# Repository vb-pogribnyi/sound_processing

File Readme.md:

## Sound Processing
This repository contains imlementation of sound localization methods. It contains parts such as:
- data generation ```Generation``` directory
- processing of open MMAUD dataset in ```Training/Processing/MMAUD```
- processing of the generated dataset(s) in  ```Training/Processing/KWave```
- implementations of top-performing models at the moment in ```Training/NN``` directory
- two most popular types of signal feature extractors: mel-spectrogram and SRP, with root file in ```Training/Data/loader.py```
- unified training pipeline in ```Training/train.py```

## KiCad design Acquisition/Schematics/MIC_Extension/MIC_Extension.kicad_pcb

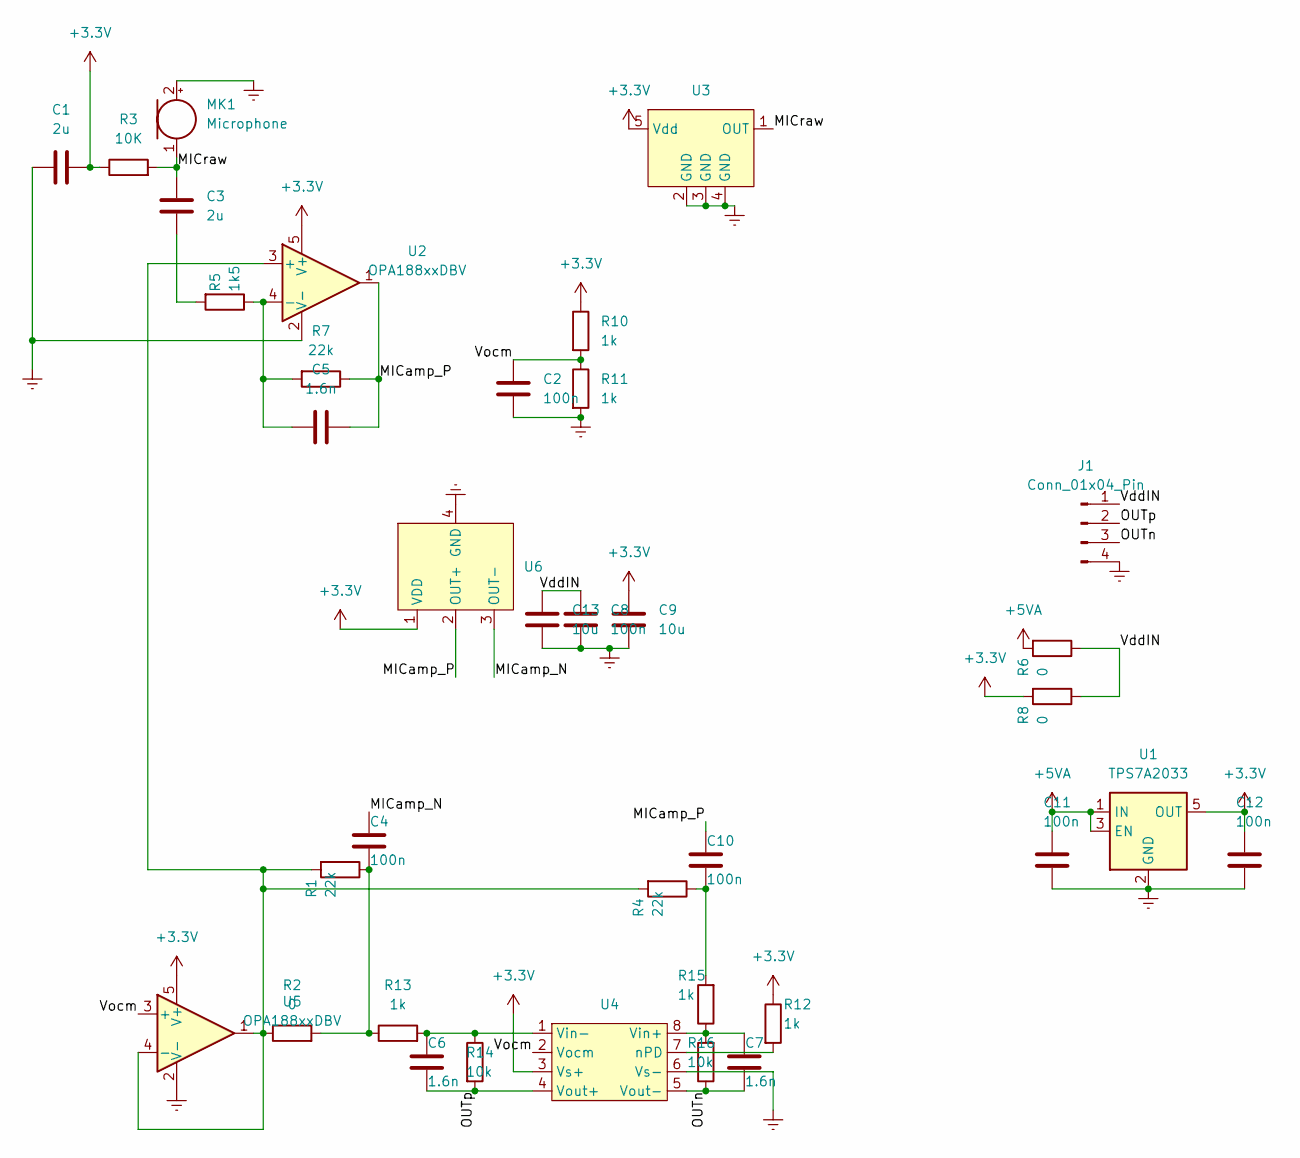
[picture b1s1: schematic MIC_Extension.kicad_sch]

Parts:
C1, C3: 2u; C_0603_1608Metric
C2, C4, C8, C10, C11, C12: 100n; C_0603_1608Metric
C5, C6, C7: 1.6n; C_0603_1608Metric
C9, C13: 10u; C_0603_1608Metric
J1: Conn_01x04_Pin; PinHeader_1x04_P2.54mm_Vertical
MK1: Microphone; PinHeader_1x02_P2.54mm_Vertical
R1, R4, R7: 22k; C_0603_1608Metric
R2, R6, R8: 0; C_0603_1608Metric
R3: 10K; C_0603_1608Metric
R5: 1k5; C_0603_1608Metric
R10, R11, R12, R13, R15: 1k; C_0603_1608Metric
R14, R16: 10k; C_0603_1608Metric
U1: TPS7A2033; SOT-23-5
U2, U5: OPA188xxDBV; TSOT-23-5
U3: AMP23
U4: VSSOP-8_3.0x3.0mm_P0.65mm
U6: ICS-40730

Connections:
+3.3V: C1.2, C9.1, C12.1, R3.1, R8.2, R10.1, R12.1, U1.5 (OUT), U2.5 (V+), U3.5 (Vdd), U4.3 (Vs+), U5.5 (V+), U6.1 (VDD)
+5VA: C11.1, R6.2, U1.1 (IN), U1.3 (EN)
/MICamp_N: C4.2, U6.3 (OUT-)
/MICamp_P: C5.2, C10.2, R7.1, U2.1, U6.2 (OUT+)
/MICraw: C3.1, MK1.1 (-), R3.2, U3.1 (OUT)
/OUTn: C7.1, J1.3, R16.1, U4.5 (Vout-)
/OUTp: C6.1, J1.2, R14.2, U4.4 (Vout+)
/VddIN: C8.1, C13.1, J1.1, R6.1, R8.1
/Vocm: C2.1, R10.2, R11.1, U4.2 (Vocm), U5.3 (+)
Earth: C1.1, C2.2, C8.2, C9.2, C11.2, C12.2, C13.2, J1.4, MK1.2 (+), R11.2, U1.2 (GND), U2.2 (V-), U3.2 (GND), U3.3 (GND), U3.4 (GND), U4.6 (Vs-), U5.2 (V-), U6.4 (GND)
unnamed: C3.2, R5.2
unnamed: C4.1, R1.1, R2.2, R13.1
unnamed: C10.1, R4.1, R15.2
unnamed: R1.2, R2.1, R4.2, U2.3 (+), U5.1, U5.4 (-)
unnamed: C5.1, R5.1, R7.2, U2.4 (-)
unnamed: C7.2, R15.1, R16.2, U4.8 (Vin+)
unnamed: C6.2, R13.2, R14.1, U4.1 (Vin-)
unnamed: R12.2, U4.7 (nPD)

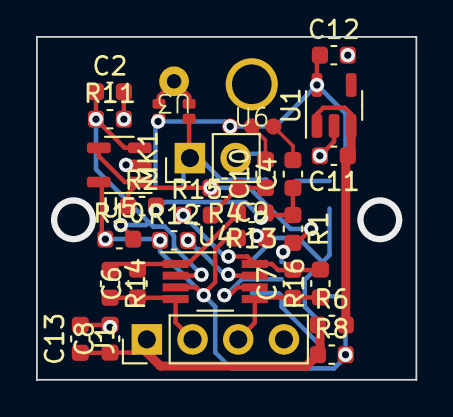
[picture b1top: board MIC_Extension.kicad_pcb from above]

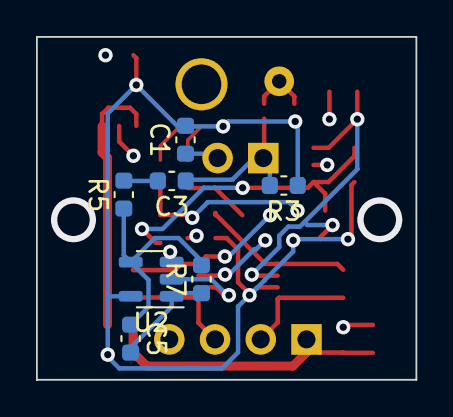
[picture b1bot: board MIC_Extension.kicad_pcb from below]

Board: 4 copper layers, 21.1 x 19.1 mm, 36 parts (7 on the bottom side), 18 nets.

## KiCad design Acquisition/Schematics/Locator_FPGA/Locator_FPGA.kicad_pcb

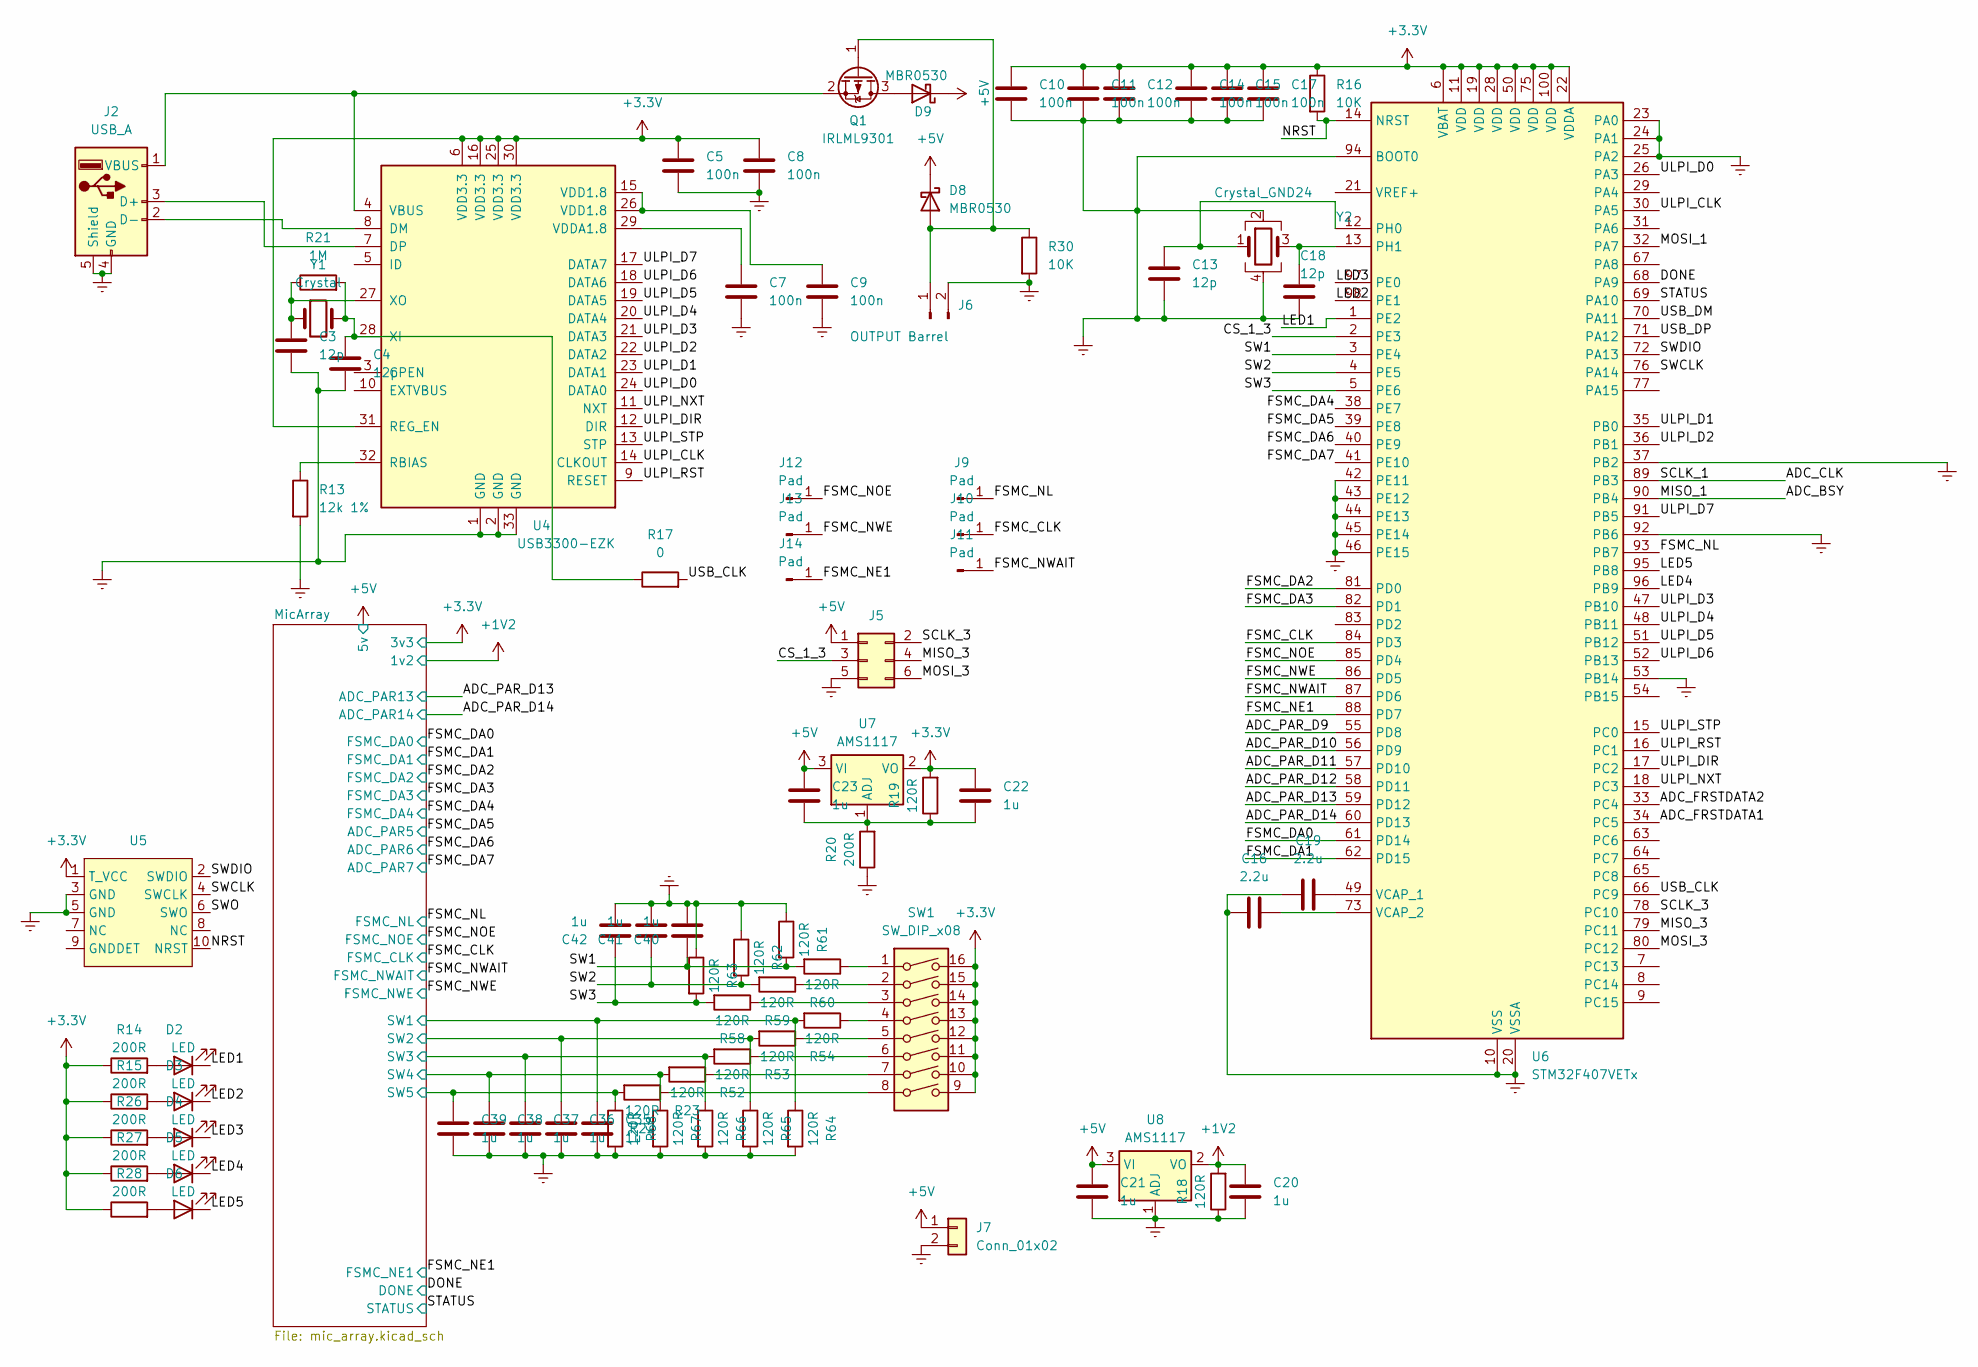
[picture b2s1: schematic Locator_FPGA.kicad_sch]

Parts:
C3, C4, C13, C18: 12p; C_0603_1608Metric
C5, C7, C8, C9: 100n; C_0603_1608Metric
C10, C11, C12, C14, C15, C17: 100n; C_0402_1005Metric
C16, C19: 2.2u; C_0603_1608Metric
C20, C21, C22, C23, C35, C36, C37, C38, C39, C40, C41, C42: 1u; C_0603_1608Metric
D2, D3, D4, D5, D6: LED; LED_0805_2012Metric
D8, D9: MBR0530; D_SOD-123
J2: USB_A; USB_A_CONNFLY_DS1095-WNR0
J5: Conn_02x03_Odd_Even; PinSocket_2x03_P2.00mm_Vertical
J6: OUTPUT Barrel; PinHeader_1x02_P2.54mm_Vertical
J7: Conn_01x02; PinHeader_1x02_P2.54mm_Vertical
J9, J10, J11, J12, J13, J14: Pad
Q1: IRLML9301; SOT-23
R13: 12k 1%; C_0603_1608Metric
R14, R15, R20, R26, R27, R28: 200R; R_0603_1608Metric
R16, R30: 10K; C_0603_1608Metric
R17: 0; C_0603_1608Metric
R18, R19, R22, R23, R52, R53, R54, R58, R59, R60, R61, R62, R63, R64, R65, R66, R67, R68: 120R; R_0603_1608Metric
R21: 1M; C_0603_1608Metric
SW1: SW_DIP_x08; DIP-16_W7.62mm
U4: USB3300-EZK; QFN-32-1EP_5x5mm_P0.5mm_EP3.45x3.45mm
U5: PinHeader_2x05_P1.27mm_Vertical_SMD
U6: STM32F407VETx; LQFP-100_14x14mm_P0.5mm
U7, U8: AMS1117; SOT-223-3_TabPin2
Y1: Crystal; Crystal_SMD_MicroCrystal_CC7V-T1A-2Pin_3.2x1.5mm
Y2: Crystal_GND24; Crystal_SMD_Abracon_ABM3C-4Pin_5.0x3.2mm

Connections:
+1V2: C20.1, R18.2, U8.2 (VO); also elsewhere on the board
+3.3V: C5.1, C8.1, C10.1, C11.1, C12.1, C14.1, C15.1, C17.1, C22.1, R14.1, R15.1, R16.1, R19.2, R26.1, R27.1, R28.1, SW1.9, SW1.10, SW1.11, SW1.12, SW1.13, SW1.14, SW1.15, SW1.16, U4.6 (VDD3.3), U4.16 (VDD3.3), U4.25 (VDD3.3), U4.30 (VDD3.3), U4.31 (REG_EN), U5.1 (T_VCC), U6.6 (VBAT), U6.11 (VDD), U6.19 (VDD), U6.22 (VDDA), U6.28 (VDD), U6.50 (VDD), U6.75 (VDD), U6.100 (VDD), U7.2 (VO); also elsewhere on the board
+5V: C21.1, C23.1, D8.1 (K), D9.1 (K), J5.1, J7.1, U7.3 (VI), U8.3 (VI); also elsewhere on the board
/ADC_BSY: U6.90 (PB4)
/ADC_CLK: U6.89 (PB3)
/ADC_FRSTDATA1: U6.34 (PC5)
/ADC_FRSTDATA2: U6.33 (PC4)
/ADC_PAR_D9: U6.55 (PD8)
/ADC_PAR_D10: U6.56 (PD9)
/ADC_PAR_D11: U6.57 (PD10)
/ADC_PAR_D12: U6.58 (PD11)
/ADC_PAR_D13: U6.59 (PD12)
/ADC_PAR_D14: U6.60 (PD13)
/CS_1_3: J5.3, U6.2 (PE3)
/DONE: U6.68 (PA9); also elsewhere on the board
/FSMC_CLK: J10.1, U6.84 (PD3); also elsewhere on the board
/FSMC_DA0: U6.61 (PD14); also elsewhere on the board
/FSMC_DA1: U6.62 (PD15); also elsewhere on the board
/FSMC_DA2: U6.81 (PD0); also elsewhere on the board
/FSMC_DA3: U6.82 (PD1); also elsewhere on the board
/FSMC_DA4: U6.38 (PE7); also elsewhere on the board
/FSMC_DA5: U6.39 (PE8); also elsewhere on the board
/FSMC_DA6: U6.40 (PE9); also elsewhere on the board
/FSMC_DA7: U6.41 (PE10); also elsewhere on the board
/FSMC_NE1: J14.1, U6.88 (PD7); also elsewhere on the board
/FSMC_NL: J9.1, U6.93 (PB7); also elsewhere on the board
/FSMC_NOE: J12.1, U6.85 (PD4); also elsewhere on the board
/FSMC_NWAIT: J11.1, U6.87 (PD6); also elsewhere on the board
/FSMC_NWE: J13.1, U6.86 (PD5); also elsewhere on the board
/LED1: D2.1 (K), U6.1 (PE2)
/LED2: D3.1 (K), U6.98 (PE1)
/LED3: D4.1 (K), U6.97 (PE0)
/LED4: D5.1 (K), U6.96 (PB9)
/LED5: D6.1 (K), U6.95 (PB8)
/MISO_3: J5.4, U6.79 (PC11)
/MOSI_1: U6.32 (PA7)
/MOSI_3: J5.6, U6.80 (PC12)
/MicArray/SW1: C35.1, R54.2, R64.1; also elsewhere on the board
/MicArray/SW2: C36.1, R53.2, R65.1; also elsewhere on the board
/MicArray/SW3: C37.1, R52.2, R66.1; also elsewhere on the board
/MicArray/SW4: C38.1, R23.2, R67.1; also elsewhere on the board
/MicArray/SW5: C39.1, R22.2, R68.1; also elsewhere on the board
/NRST: R16.2, U5.10 (NRST), U6.14 (NRST)
/SCLK_3: J5.2, U6.78 (PC10)
/STATUS: U6.69 (PA10); also elsewhere on the board
/SW1: C40.1, R60.2, R61.2, U6.3 (PE4)
/SW2: C41.1, R59.2, R62.2, U6.4 (PE5)
/SW3: C42.1, R58.2, R63.2, U6.5 (PE6)
/SWCLK: U5.4 (SWCLK), U6.76 (PA14)
/SWDIO: U5.2 (SWDIO), U6.72 (PA13)
/SWO: U5.6 (SWO)
/ULPI_CLK: U4.14 (CLKOUT), U6.30 (PA5)
/ULPI_D0: U4.24 (DATA0), U6.26 (PA3)
/ULPI_D1: U4.23 (DATA1), U6.35 (PB0)
/ULPI_D2: U4.22 (DATA2), U6.36 (PB1)
/ULPI_D3: U4.21 (DATA3), U6.47 (PB10)
/ULPI_D4: U4.20 (DATA4), U6.48 (PB11)
/ULPI_D5: U4.19 (DATA5), U6.51 (PB12)
/ULPI_D6: U4.18 (DATA6), U6.52 (PB13)
/ULPI_D7: U4.17 (DATA7), U6.91 (PB5)
/ULPI_DIR: U4.12 (DIR), U6.17 (PC2)
/ULPI_NXT: U4.11 (NXT), U6.18 (PC3)
/ULPI_RST: U4.9 (RESET), U6.16 (PC1)
/ULPI_STP: U4.13 (STP), U6.15 (PC0)
/USB_CLK: R17.2, U6.66 (PC9)
/USB_DM: U6.70 (PA11)
/USB_DP: U6.71 (PA12)
Earth: C3.2, C4.2, C5.2, C7.2, C8.2, C9.2, C10.2, C11.2, C12.2, C13.2, C14.2, C15.2, C16.1, C17.2, C18.2, C19.1, C20.2, C21.2, C35.2, C36.2, C37.2, C38.2, C39.2, C40.2, C41.2, C42.2, J2.4 (GND), J2.5 (Shield), J5.5, J6.2, J7.2, R13.2, R18.1, R20.1, R30.2, R61.1, R62.1, R63.1, R64.2, R65.2, R66.2, R67.2, R68.2, U4.1 (GND), U4.2 (GND), U4.33 (GND), U5.3 (GND), U5.5 (GND), U6.10 (VSS), U6.20 (VSSA), U6.23 (PA0), U6.24 (PA1), U6.25 (PA2), U6.27 (VSS), U6.37 (PB2), U6.42 (PE11), U6.43 (PE12), U6.44 (PE13), U6.45 (PE14), U6.46 (PE15), U6.53 (PB14), U6.74 (VSS), U6.92 (PB6), U6.94 (BOOT0), U6.99 (VSS), U8.1 (ADJ), Y2.2, Y2.4; also elsewhere on the board
unnamed: C9.1, U4.15 (VDD1.8), U4.26 (VDD1.8)
unnamed: D2.2 (A), R14.2
unnamed: D3.2 (A), R15.2
unnamed: D4.2 (A), R26.2
unnamed: D5.2 (A), R27.2
unnamed: D6.2 (A), R28.2
unnamed: D8.2 (A), J6.1, Q1.1 (G), R30.1
unnamed: D9.2 (A), Q1.3 (D)
unnamed: J2.3 (D+), U4.7 (DP)
unnamed: J2.2 (D-), U4.8 (DM)
unnamed: J2.1 (VBUS), Q1.2 (S), U4.4 (VBUS)
unnamed: R22.1, SW1.8
unnamed: R23.1, SW1.7
unnamed: R52.1, SW1.6
unnamed: R53.1, SW1.5
unnamed: R54.1, SW1.4
unnamed: R58.1, SW1.3
unnamed: R59.1, SW1.2
unnamed: R60.1, SW1.1
unnamed: R13.1, U4.32 (RBIAS)
unnamed: C7.1, U4.29 (VDDA1.8)
unnamed: C4.1, R17.1, R21.2, U4.28 (XI), Y1.2
unnamed: C3.1, R21.1, U4.27 (XO), Y1.1
unnamed: C13.1, U6.12 (PH0), Y2.1
unnamed: C18.1, U6.13 (PH1), Y2.3
unnamed: C19.2, U6.49 (VCAP_1)
unnamed: C16.2, U6.73 (VCAP_2)
unnamed: C22.2, C23.2, R19.1, R20.2, U7.1 (ADJ)

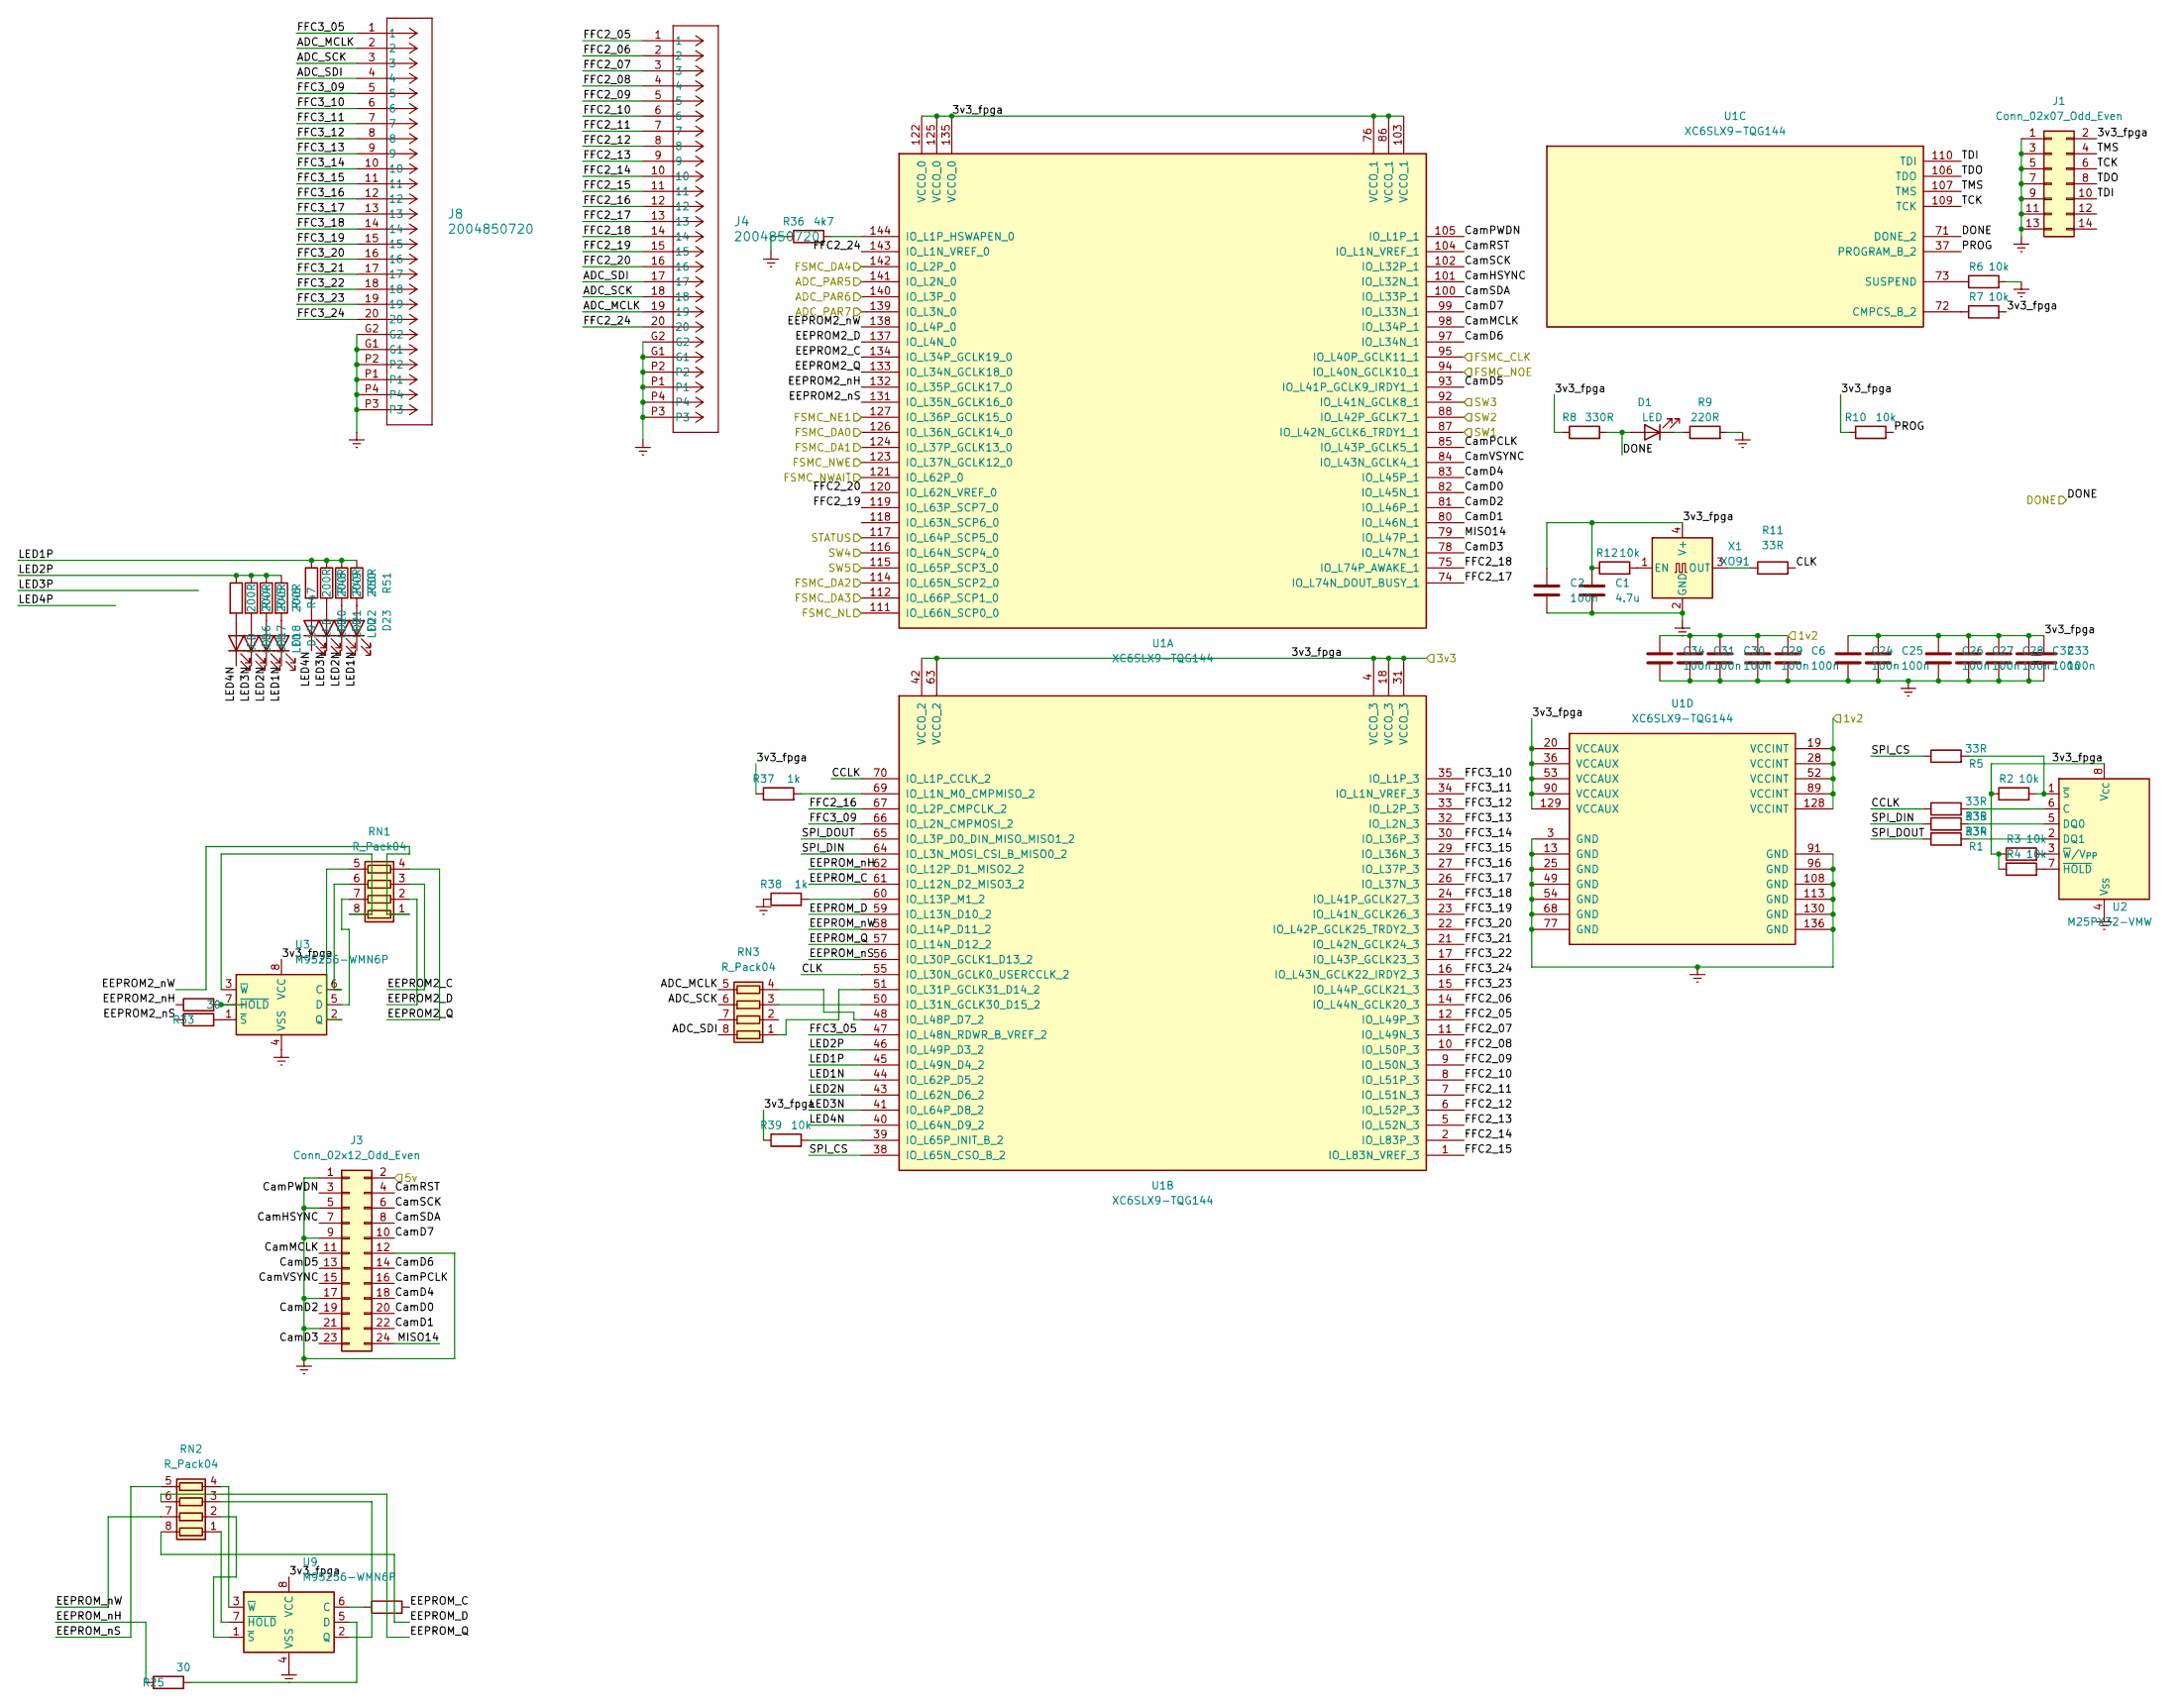
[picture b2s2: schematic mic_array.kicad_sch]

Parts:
C1: 4.7u; R_0603_1608Metric
C2: 100n; R_0603_1608Metric
C6, C24, C25, C26, C27, C28, C29, C30, C31, C32, C33, C34: 100n; C_0402_1005Metric
D1, D16, D17, D18, D19, D20, D21, D22, D23: LED; LED_0805_2012Metric
J1: Conn_02x07_Odd_Even; PinHeader_2x07_P2.00mm_Vertical
J3: Conn_02x12_Odd_Even; PinHeader_2x12_P2.54mm_Vertical
J4, J8: 2004850720; Molex FFC 20pin sideways
R1, R5, R11, R34, R35: 33R; R_0603_1608Metric
R2, R3, R4, R6, R7, R10, R12, R39: 10k; R_0603_1608Metric
R8: 330R; R_0603_1608Metric
R9: 220R; R_0603_1608Metric
R24, R25, R29, R33: 30; R_0603_1608Metric
R36: 4k7; R_0603_1608Metric
R37, R38: 1k; R_0603_1608Metric
R44, R45, R46, R47, R48, R49, R50, R51: 200R; R_0603_1608Metric
RN1, RN2, RN3: R_Pack04; R_Array_Concave_4x0402
U1: XC6SLX9-TQG144; TQFP-144_20x20mm_P0.5mm
U2: M25PX32-VMW; SOIC-8W_5.3x5.3mm_P1.27mm
U3, U9: M95256-WMN6P; SOIC-8_3.9x4.9mm_P1.27mm
X1: XO91; Oscillator_SMD_EuroQuartz_XO91-4Pin_7.0x5.0mm

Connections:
+1V2: C6.1, C29.1, C30.1, C31.1, C34.1, U1.19 (VCCINT), U1.28 (VCCINT), U1.52 (VCCINT), U1.89 (VCCINT), U1.128 (VCCINT); also elsewhere on the board
+3.3V: C1.1, C2.1, C24.1, C25.1, C26.1, C27.1, C28.1, C32.1, C33.1, J1.2, R2.1, R3.1, R4.1, R7.2, R8.1, R10.1, R12.1, R37.1, R39.1, U1.4 (VCCO_3), U1.18 (VCCO_3), U1.20 (VCCAUX), U1.31 (VCCO_3), U1.36 (VCCAUX), U1.42 (VCCO_2), U1.53 (VCCAUX), U1.63 (VCCO_2), U1.76 (VCCO_1), U1.86 (VCCO_1), U1.90 (VCCAUX), U1.103 (VCCO_1), U1.122 (VCCO_0), U1.125 (VCCO_0), U1.129 (VCCAUX), U1.135 (VCCO_0), U2.8 (V_{CC}), U3.8 (VCC), U9.8 (VCC), X1.4 (V+); also elsewhere on the board
+5V: J3.2; also elsewhere on the board
/DONE: D1.2 (A), R8.2, U1.71 (DONE_2); also elsewhere on the board
/FSMC_CLK: U1.95 (IO_L40P_GCLK11_1); also elsewhere on the board
/FSMC_DA0: U1.126 (IO_L36N_GCLK14_0); also elsewhere on the board
/FSMC_DA1: U1.124 (IO_L37P_GCLK13_0); also elsewhere on the board
/FSMC_DA2: U1.114 (IO_L65N_SCP2_0); also elsewhere on the board
/FSMC_DA3: U1.112 (IO_L66P_SCP1_0); also elsewhere on the board
/FSMC_DA4: U1.142 (IO_L2P_0); also elsewhere on the board
/FSMC_DA5: U1.141 (IO_L2N_0); also elsewhere on the board
/FSMC_DA6: U1.140 (IO_L3P_0); also elsewhere on the board
/FSMC_DA7: U1.139 (IO_L3N_0); also elsewhere on the board
/FSMC_NE1: U1.127 (IO_L36P_GCLK15_0); also elsewhere on the board
/FSMC_NL: U1.111 (IO_L66N_SCP0_0); also elsewhere on the board
/FSMC_NOE: U1.94 (IO_L40N_GCLK10_1); also elsewhere on the board
/FSMC_NWAIT: U1.121 (IO_L62P_0); also elsewhere on the board
/FSMC_NWE: U1.123 (IO_L37N_GCLK12_0); also elsewhere on the board
/MicArray/ADC_MCLK: J4.19, J8.2, RN3.5 (R4.2)
/MicArray/ADC_SCK: J4.18, J8.3, RN3.6 (R3.2)
/MicArray/ADC_SDI: J4.17, J8.4, RN3.8 (R1.2)
/MicArray/CCLK: R35.1, U1.70 (IO_L1P_CCLK_2)
/MicArray/CLK: R11.2, U1.55 (IO_L30N_GCLK0_USERCCLK_2)
/MicArray/CamD0: J3.20, U1.82 (IO_L45N_1)
/MicArray/CamD1: J3.22, U1.80 (IO_L46N_1)
/MicArray/CamD2: J3.19, U1.81 (IO_L46P_1)
/MicArray/CamD3: J3.23, U1.78 (IO_L47N_1)
/MicArray/CamD4: J3.18, U1.83 (IO_L45P_1)
/MicArray/CamD5: J3.13, U1.93 (IO_L41P_GCLK9_IRDY1_1)
/MicArray/CamD6: J3.14, U1.97 (IO_L34N_1)
/MicArray/CamD7: J3.10, U1.99 (IO_L33N_1)
/MicArray/CamHSYNC: J3.7, U1.101 (IO_L32N_1)
/MicArray/CamMCLK: J3.11, U1.98 (IO_L34P_1)
/MicArray/CamPCLK: J3.16, U1.85 (IO_L43P_GCLK5_1)
/MicArray/CamPWDN: J3.3, U1.105 (IO_L1P_1)
/MicArray/CamRST: J3.4, U1.104 (IO_L1N_VREF_1)
/MicArray/CamSCK: J3.6, U1.102 (IO_L32P_1)
/MicArray/CamSDA: J3.8, U1.100 (IO_L33P_1)
/MicArray/CamVSYNC: J3.15, U1.84 (IO_L43N_GCLK4_1)
/MicArray/EEPROM2_C: RN1.3 (R3.1), U1.134 (IO_L34P_GCLK19_0)
/MicArray/EEPROM2_D: RN1.2 (R2.1), U1.137 (IO_L4N_0)
/MicArray/EEPROM2_Q: RN1.4 (R4.1), U1.133 (IO_L34N_GCLK18_0)
/MicArray/EEPROM2_nH: R24.1, U1.132 (IO_L35P_GCLK17_0)
/MicArray/EEPROM2_nS: R33.1, U1.131 (IO_L35N_GCLK16_0)
/MicArray/EEPROM2_nW: RN1.1 (R1.1), U1.138 (IO_L4P_0)
/MicArray/EEPROM_C: R29.2, U1.61 (IO_L12N_D2_MISO3_2)
/MicArray/EEPROM_D: RN2.8 (R1.2), U1.59 (IO_L13N_D10_2)
/MicArray/EEPROM_Q: RN2.6 (R3.2), U1.57 (IO_L14N_D12_2)
/MicArray/EEPROM_nH: R25.1, U1.62 (IO_L12P_D1_MISO2_2)
/MicArray/EEPROM_nS: RN2.5 (R4.2), U1.56 (IO_L30P_GCLK1_D13_2)
/MicArray/EEPROM_nW: RN2.7 (R2.2), U1.58 (IO_L14P_D11_2)
/MicArray/FFC2_05: J4.1, U1.12 (IO_L49P_3)
/MicArray/FFC2_06: J4.2, U1.14 (IO_L44N_GCLK20_3)
/MicArray/FFC2_07: J4.3, U1.11 (IO_L49N_3)
/MicArray/FFC2_08: J4.4, U1.10 (IO_L50P_3)
/MicArray/FFC2_09: J4.5, U1.9 (IO_L50N_3)
/MicArray/FFC2_10: J4.6, U1.8 (IO_L51P_3)
/MicArray/FFC2_11: J4.7, U1.7 (IO_L51N_3)
/MicArray/FFC2_12: J4.8, U1.6 (IO_L52P_3)
/MicArray/FFC2_13: J4.9, U1.5 (IO_L52N_3)
/MicArray/FFC2_14: J4.10, U1.2 (IO_L83P_3)
/MicArray/FFC2_15: J4.11, U1.1 (IO_L83N_VREF_3)
/MicArray/FFC2_16: J4.12, U1.67 (IO_L2P_CMPCLK_2)
/MicArray/FFC2_17: J4.13, U1.74 (IO_L74N_DOUT_BUSY_1)
/MicArray/FFC2_18: J4.14, U1.75 (IO_L74P_AWAKE_1)
/MicArray/FFC2_19: J4.15, U1.119 (IO_L63P_SCP7_0)
/MicArray/FFC2_20: J4.16, U1.120 (IO_L62N_VREF_0)
/MicArray/FFC2_24: J4.20, U1.143 (IO_L1N_VREF_0)
/MicArray/FFC3_05: J8.1, U1.47 (IO_L48N_RDWR_B_VREF_2)
/MicArray/FFC3_09: J8.5, U1.66 (IO_L2N_CMPMOSI_2)
/MicArray/FFC3_10: J8.6, U1.35 (IO_L1P_3)
/MicArray/FFC3_11: J8.7, U1.34 (IO_L1N_VREF_3)
/MicArray/FFC3_12: J8.8, U1.33 (IO_L2P_3)
/MicArray/FFC3_13: J8.9, U1.32 (IO_L2N_3)
/MicArray/FFC3_14: J8.10, U1.30 (IO_L36P_3)
/MicArray/FFC3_15: J8.11, U1.29 (IO_L36N_3)
/MicArray/FFC3_16: J8.12, U1.27 (IO_L37P_3)
/MicArray/FFC3_17: J8.13, U1.26 (IO_L37N_3)
/MicArray/FFC3_18: J8.14, U1.24 (IO_L41P_GCLK27_3)
/MicArray/FFC3_19: J8.15, U1.23 (IO_L41N_GCLK26_3)
/MicArray/FFC3_20: J8.16, U1.22 (IO_L42P_GCLK25_TRDY2_3)
/MicArray/FFC3_21: J8.17, U1.21 (IO_L42N_GCLK24_3)
/MicArray/FFC3_22: J8.18, U1.17 (IO_L43P_GCLK23_3)
/MicArray/FFC3_23: J8.19, U1.15 (IO_L44P_GCLK21_3)
/MicArray/FFC3_24: J8.20, U1.16 (IO_L43N_GCLK22_IRDY2_3)
/MicArray/LED1N: D19.1 (K), D23.1 (K), U1.44 (IO_L62P_D5_2)
/MicArray/LED1P: R48.1, R49.1, R50.1, R51.1, U1.45 (IO_L49N_D4_2)
/MicArray/LED2N: D18.1 (K), D22.1 (K), U1.43 (IO_L62N_D6_2)
/MicArray/LED2P: R44.1, R45.1, R46.1, R47.1, U1.46 (IO_L49P_D3_2)
/MicArray/LED3N: D17.1 (K), D21.1 (K), U1.41 (IO_L64P_D8_2)
/MicArray/LED4N: D16.1 (K), D20.1 (K), U1.40 (IO_L64N_D9_2)
/MicArray/MISO14: J3.24, U1.79 (IO_L47P_1)
/MicArray/PROG: R10.2, U1.37 (PROGRAM_B_2)
/MicArray/SPI_CS: R5.1, U1.38 (IO_L65N_CSO_B_2)
/MicArray/SPI_DIN: R34.1, U1.64 (IO_L3N_MOSI_CSI_B_MISO0_2)
/MicArray/SPI_DOUT: R1.1, U1.65 (IO_L3P_D0_DIN_MISO_MISO1_2)
/MicArray/SW1: U1.87 (IO_L42N_GCLK6_TRDY1_1); also elsewhere on the board
/MicArray/SW2: U1.88 (IO_L42P_GCLK7_1); also elsewhere on the board
/MicArray/SW3: U1.92 (IO_L41N_GCLK8_1); also elsewhere on the board
/MicArray/SW4: U1.116 (IO_L64N_SCP4_0); also elsewhere on the board
/MicArray/SW5: U1.115 (IO_L65P_SCP3_0); also elsewhere on the board
/MicArray/TCK: J1.6, U1.109 (TCK)
/MicArray/TDI: J1.10, U1.110 (TDI)
/MicArray/TDO: J1.8, U1.106 (TDO)
/MicArray/TMS: J1.4, U1.107 (TMS)
/STATUS: U1.117 (IO_L64P_SCP5_0); also elsewhere on the board
Earth: C1.2, C2.2, C6.2, C24.2, C25.2, C26.2, C27.2, C28.2, C29.2, C30.2, C31.2, C32.2, C33.2, C34.2, J1.1, J1.3, J1.5, J1.7, J1.9, J1.11, J1.13, J3.1, J3.5, J3.9, J3.12, J3.17, J3.21, J4.G1, J4.G2, J4.P1, J4.P2, J4.P3, J4.P4, J8.G1, J8.G2, J8.P1, J8.P2, J8.P3, J8.P4, R6.2, R9.2, R36.1, R38.1, U1.3 (GND), U1.13 (GND), U1.25 (GND), U1.49 (GND), U1.54 (GND), U1.68 (GND), U1.77 (GND), U1.91 (GND), U1.96 (GND), U1.108 (GND), U1.113 (GND), U1.130 (GND), U1.136 (GND), U2.4 (V_{SS}), U3.4 (VSS), U9.4 (VSS), X1.2 (GND); also elsewhere on the board
unnamed: D1.1 (K), R9.1
unnamed: D16.2 (A), R44.2
unnamed: D17.2 (A), R45.2
unnamed: D18.2 (A), R46.2
unnamed: D19.2 (A), R47.2
unnamed: D20.2 (A), R48.2
unnamed: D21.2 (A), R49.2
unnamed: D22.2 (A), R50.2
unnamed: D23.2 (A), R51.2
unnamed: RN1.8 (R1.2), U3.3 (~W)
unnamed: RN1.7 (R2.2), U3.5 (D)
unnamed: RN1.6 (R3.2), U3.6 (C)
unnamed: RN1.5 (R4.2), U3.2 (Q)
unnamed: RN2.1 (R1.1), U9.7 (~HOLD)
unnamed: RN2.2 (R2.1), U9.1 (~S)
unnamed: RN2.3 (R3.1), U9.2 (Q)
unnamed: RN2.4 (R4.1), U9.3 (~W)
unnamed: RN3.1 (R1.1), U1.51 (IO_L31P_GCLK31_D14_2)
unnamed: RN3.3 (R3.1), U1.50 (IO_L31N_GCLK30_D15_2)
unnamed: RN3.4 (R4.1), U1.48 (IO_L48P_D7_2)
unnamed: R36.2, U1.144 (IO_L1P_HSWAPEN_0)
unnamed: R37.2, U1.69 (IO_L1N_M0_CMPMISO_2)
unnamed: R38.2, U1.60 (IO_L13P_M1_2)
unnamed: R39.2, U1.39 (IO_L65P_INIT_B_2)
unnamed: R7.1, U1.72 (CMPCS_B_2)
unnamed: R6.1, U1.73 (SUSPEND)
unnamed: R35.2, U2.6 (C)
unnamed: R34.2, U2.5 (DQ0)
unnamed: R1.2, U2.2 (DQ1)
unnamed: R4.2, U2.7 (~HOLD)
unnamed: R2.2, R5.2, U2.1 (~S)
unnamed: R3.2, U2.3 (~W/V_{PP})
unnamed: R24.2, U3.7 (~HOLD)
unnamed: R33.2, U3.1 (~S)
unnamed: R29.1, U9.6 (C)
unnamed: R25.2, U9.5 (D)
unnamed: R12.2, X1.1 (EN)
unnamed: R11.1, X1.3 (OUT)

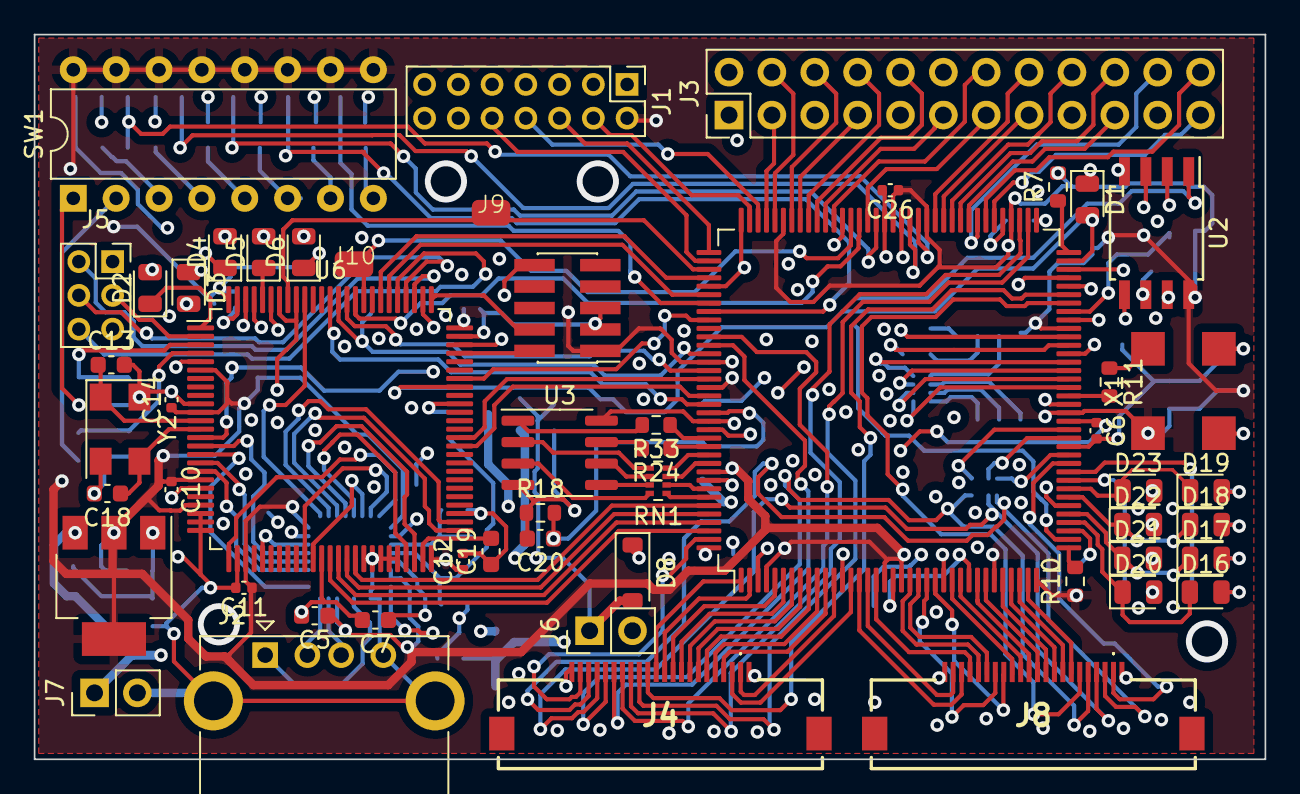
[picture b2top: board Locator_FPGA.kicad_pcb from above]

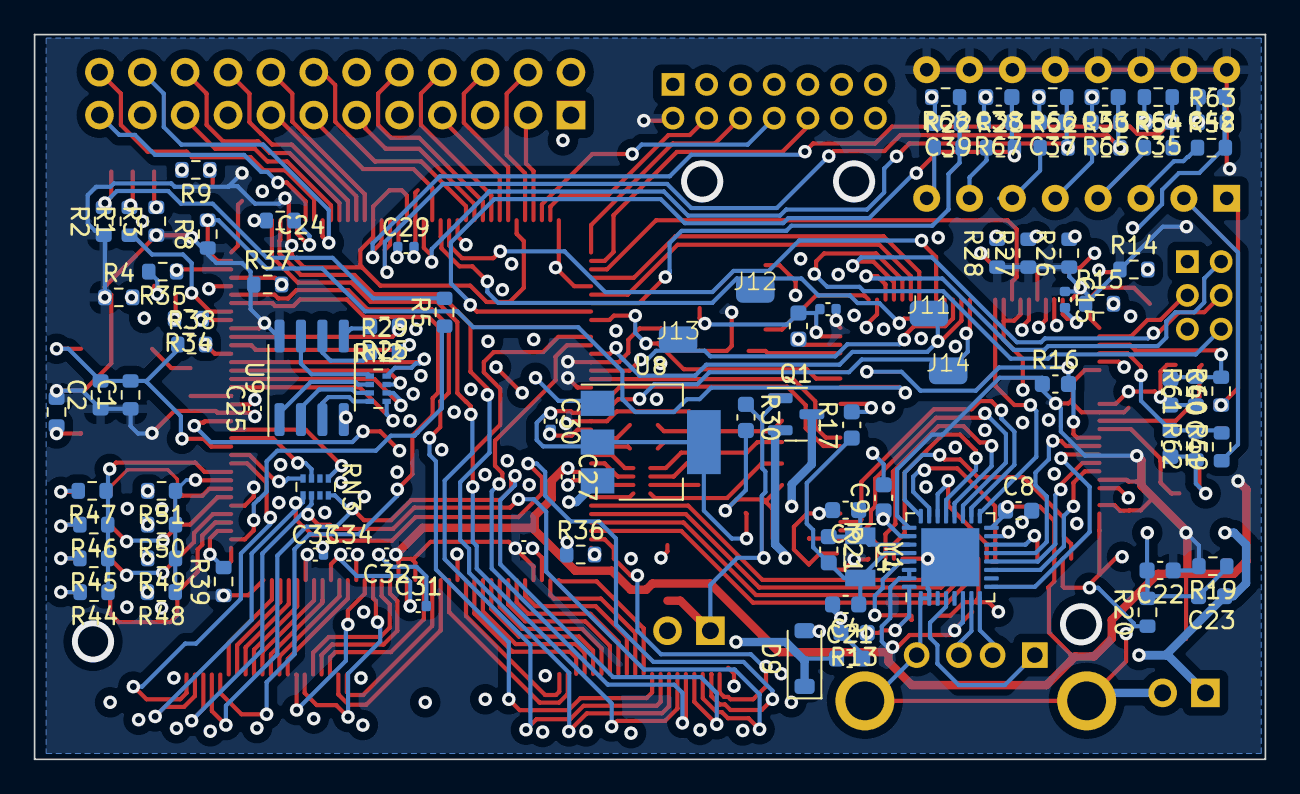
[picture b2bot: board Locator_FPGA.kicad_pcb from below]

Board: 4 copper layers, 72.9 x 42.9 mm, 148 parts (95 on the bottom side), 202 nets.
